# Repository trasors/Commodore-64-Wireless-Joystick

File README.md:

# Commodore 64 Wireless Joystick

A DIY wireless joystick system for the Commodore 64, using nRF24L01+ wireless modules and ATtiny/ATmega microcontrollers. The system consists of two main components:

* **Receiver (RX):** An ATtiny-based receiver that interfaces with the Commodore 64 dual joystick ports.
* **Transmitter (TX):** An ATmega-based wireless joystick controller.

## 1. Disclaimer

This project is provided **as-is**, without any guarantees of functionality or reliability etc. I built it in 2019 from various microcontrollers I was using at that time. It is not actively developed or maintained and uses hardware components and software libraries that are likely outdated. I am sharing as it may be useful for others for learning purposes or as a starting point to update and modernise. The useful bit is the C64 receiver PCB and code. The joystick / transmitter was mainly built for MAME use and the C64 receiver only handles a subset of the buttons.

## 2. Hardware Design

The EAGLE design files are located in the [`eagle/`](eagle/) directory. To modify, you may need to install the library file (.lbr)

### 2.1 Transmitter (TX)

The transmitter uses an ATmega328p microcontroller to read joystick inputs and send the corresponding button and directional states wirelessly via an nRF24L01+ transceiver. An MCP23008 was added to handle the extra buttons for MAME. A TP4056 module was added to charge a Lipo battery which powers the joystick.

| PCB Layout | Top | Bottom |
| --- | --- | --- |
|  |  |  |

### 2.2 Receiver (RX)

The receiver uses an ATtiny 1634 microcontroller and an nRF24L01+ transceiver to receive joystick data and translate it into signals compatible with the Commodore 64 joystick port. For more information on the pin mapping see [control port mapping](docs/C64ControlPort.md). Note, pots / analog axes are not implemented in the hardware.

| PCB Layout | Overview | Top | Bottom |
| --- | --- | --- | --- |
|  |  |  |  |

### 2.3 Bill of Materials (BOM)

Here is a list of the main components. Refer to the EAGLE schematics for exact component, values, quantities, and specifications etc.

#### Receiver
```
1 x ATTiny 1634
1 x nRF24L01+
1 x MCP1700 3.3V
2 x 9-pin D-SUB Female (PCB board mount variety)
```
#### Transmitter
```
1 x ATMega 328p QFP32
1 x nRF24L01+
1 x TP4056 (for LIPO battery and USB charging)
1 x Joystick, various buttons and a couple of pots
1 x MCP1700 3.3V
```
## 3. Firmware and Code

The firmware is located in the [`code/`](code/) directory. The code is divided into two main parts:

* **TX firmware:** Runs on the ATmega, reads the joystick inputs, and transmits their states over the nRF24 wireless link.
* **RX firmware:** Runs on the ATtiny, receives the wireless data, and translates it into the appropriate signals for the Commodore 64 joystick interface.

Notes on the [packet format](docs/PacketFormat.md):
* Analog axes are not implemented in the RX code
* Buttons 1-8 (except 5) register a button press on the C64 receiver
* Button 5 is used to toggle joystick 1 and 2 on the C64 receiver

### 3.1 Source Code

```text
code/
├── c64-wireless-joystick-tx/
│   └── c64-wireless-joystick-tx.ino
└── c64-wireless-joystick-rx/
    └── c64-wireless-joystick-rx.ino
```

### 3.2 Building and Uploading

The Arduino 1.8.8 IDE was use to compile the code.

### 3.3 Libraries and Dependencies

The firmware depends on the following external libraries: -

* https://github.com/nRF24/RF24
* https://github.com/spencekonde/attinycore
* https://github.com/adafruit/adafruit-mcp23008-library

*Note: This project uses the versions available in 2019/20. Current versions may not work!*

## 4. Hardware Build

Here are some pictures of the final build

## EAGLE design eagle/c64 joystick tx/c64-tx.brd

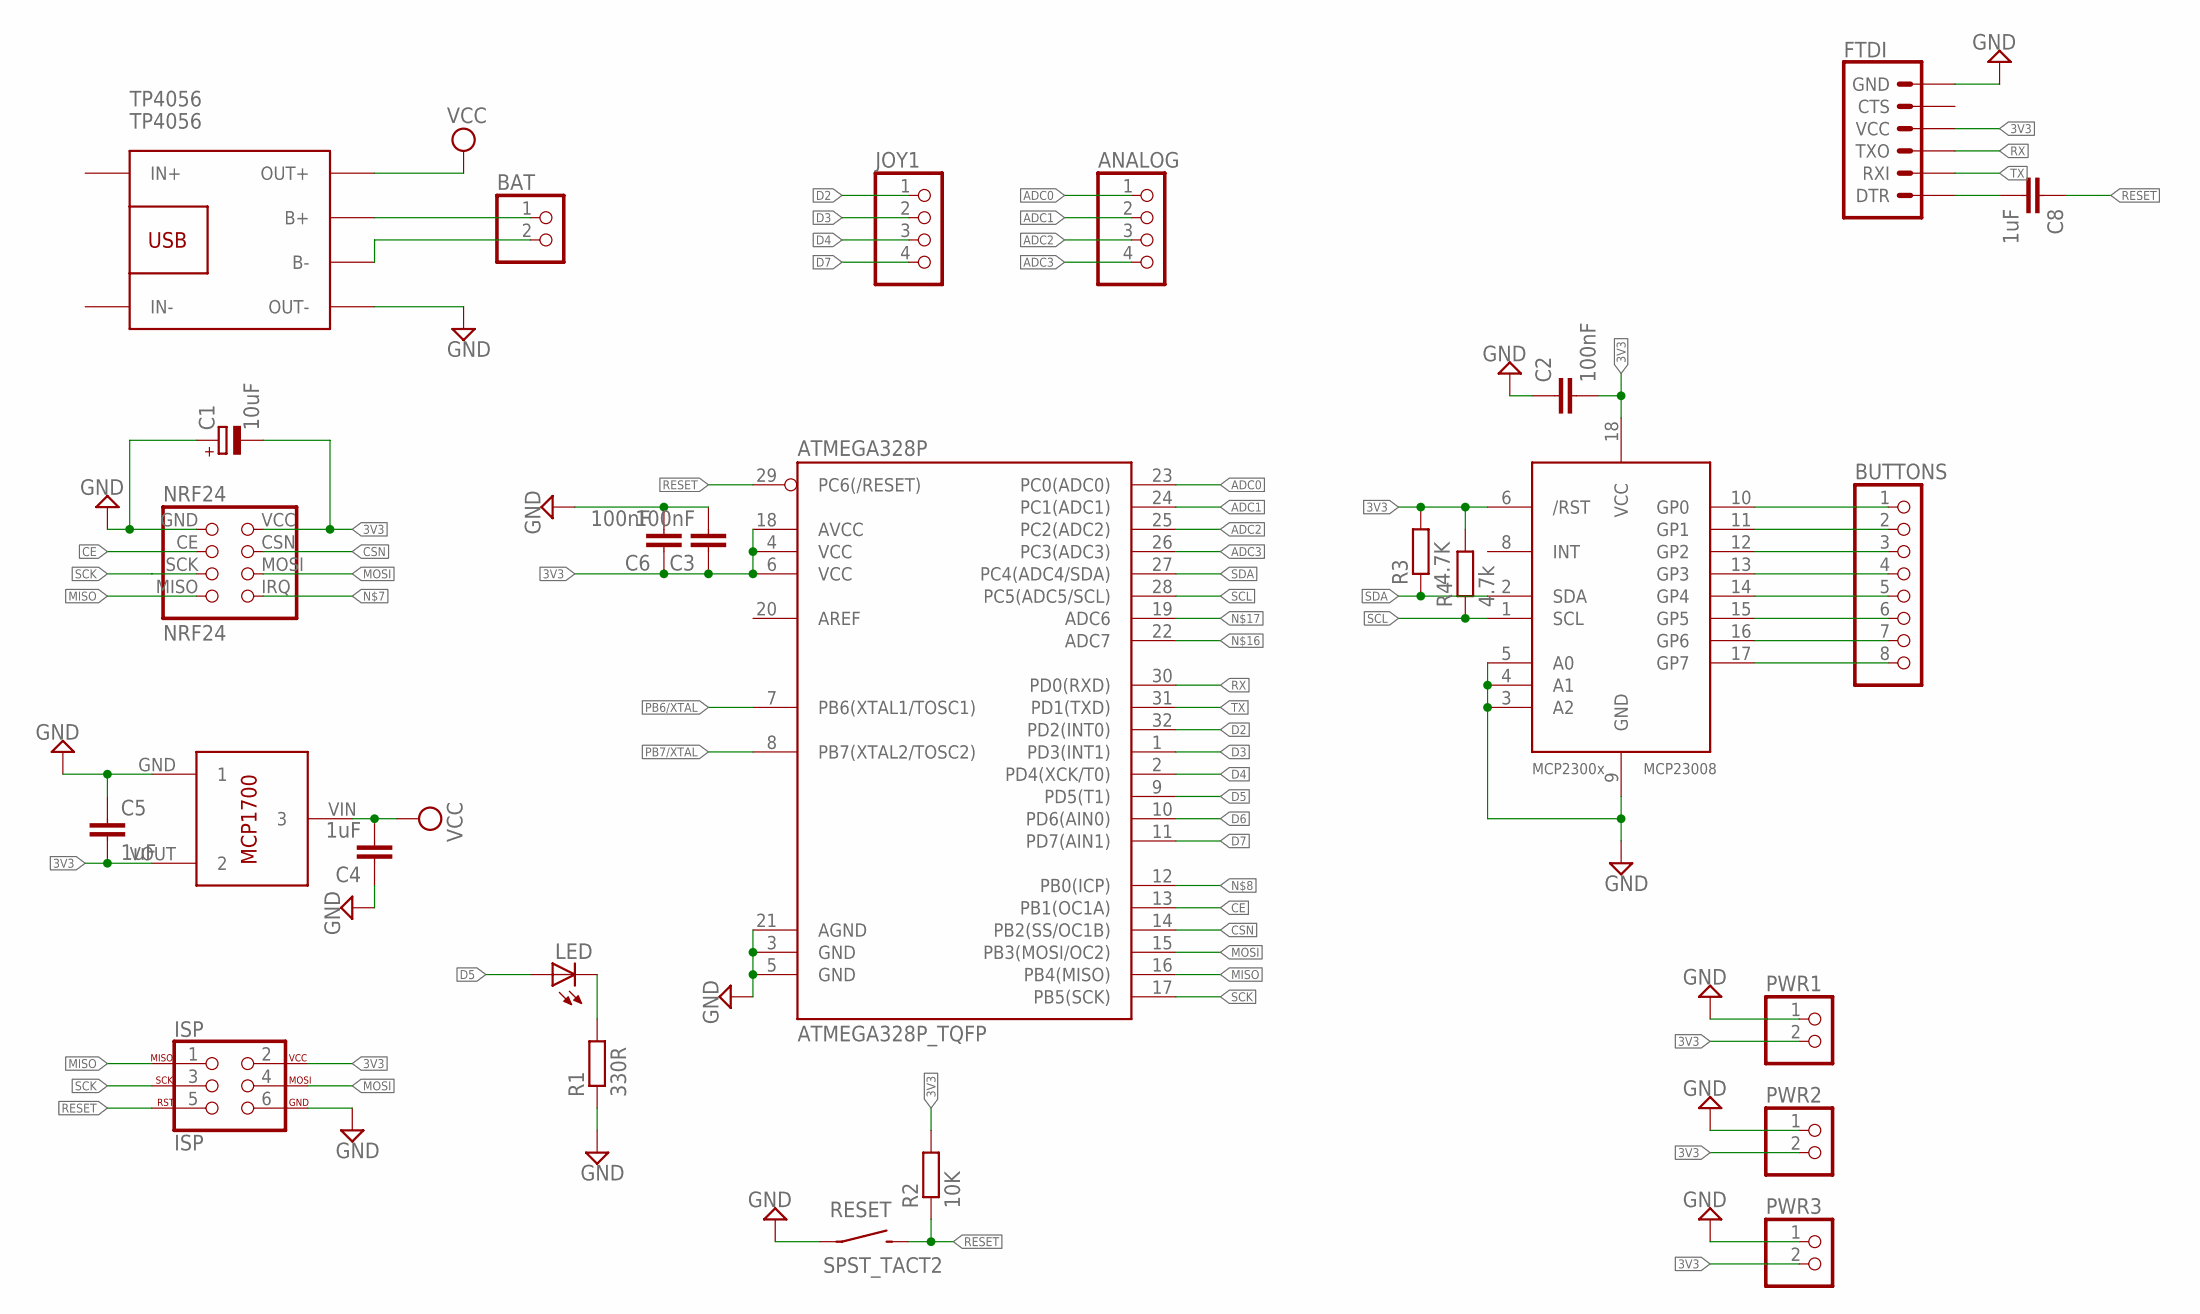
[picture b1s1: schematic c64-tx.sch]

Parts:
ANALOG: PINHD-1X4; 1X04
ATMEGA328P: ATMEGA328P_TQFP; TQFP32-08
BAT: PINHD-1X2; 1X02
BUTTONS: PINHD-1X8; 1X08
C1: 10uF; A/3216-18W
C2, C3, C6: 100nF; C1206K
C4, C5, C8: 1uF; C1206K
FTDI: 6_PIN_SERIAL_TARGETPTH-KIT; 1X06-KIT
ISP: ISP; 2X3-NS
JOY1: PINHD-1X4; 1X04
LED: LEDSMT1206; 1206
MCP1700: MCP1700T-3302E/TT
MCP23008: MCP23008/SO; SO18W
NRF24: NRF24; NRF24-PCB
PWR1, PWR2, PWR3: PINHD-1X2; 1X02
R1: 330R; M1206
R2: 10K; M1206
R3: 4.7K; M1206
R4: 4.7k; M1206
RESET: SPST_TACT2; 6MMTACTILE
TP4056: TP4056; BATTERY-CHARGER-LI-PROT

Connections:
3V3: ATMEGA328P.4 (VCC), ATMEGA328P.6 (VCC), ATMEGA328P.18 (AVCC), C1.-, C2.2, C3.1, C5.2, C6.1, FTDI.4 (VCC), ISP.2, MCP1700.VOUT (2), MCP23008.6 (/RST), MCP23008.18 (VCC), NRF24.VCC, PWR1.2, PWR2.2, PWR3.2, R2.2, R3.2, R4.2
ADC0: ANALOG.1, ATMEGA328P.23 (PC0(ADC0))
ADC1: ANALOG.2, ATMEGA328P.24 (PC1(ADC1))
ADC2: ANALOG.3, ATMEGA328P.25 (PC2(ADC2))
ADC3: ANALOG.4, ATMEGA328P.26 (PC3(ADC3))
B+: BAT.1, TP4056.B+
B-: BAT.2, TP4056.B-
CE: ATMEGA328P.13 (PB1(OC1A)), NRF24.CE
CSN: ATMEGA328P.14 (PB2(SS/OC1B)), NRF24.CSN
D2: ATMEGA328P.32 (PD2(INT0)), JOY1.1
D3: ATMEGA328P.1 (PD3(INT1)), JOY1.2
D4: ATMEGA328P.2 (PD4(XCK/T0)), JOY1.3
D5: ATMEGA328P.9 (PD5(T1)), LED.A
D6: ATMEGA328P.10 (PD6(AIN0))
D7: ATMEGA328P.11 (PD7(AIN1)), JOY1.4
GND: ATMEGA328P.3 (GND), ATMEGA328P.5 (GND), ATMEGA328P.21 (AGND), C1.+, C2.1, C3.2, C4.1, C5.1, C6.2, FTDI.6 (GND), ISP.6, MCP1700.GND (1), MCP23008.3 (A2), MCP23008.4 (A1), MCP23008.5 (A0), MCP23008.9 (GND), NRF24.GND, PWR1.1, PWR2.1, PWR3.1, R1.1, RESET.P$1, TP4056.OUT-
MISO: ATMEGA328P.16 (PB4(MISO)), ISP.1, NRF24.MISO
MOSI: ATMEGA328P.15 (PB3(MOSI/OC2)), ISP.4, NRF24.MOSI
unnamed: BUTTONS.1, MCP23008.10 (GP0)
unnamed: LED.C, R1.2
unnamed: BUTTONS.2, MCP23008.11 (GP1)
unnamed: BUTTONS.3, MCP23008.12 (GP2)
unnamed: BUTTONS.4, MCP23008.13 (GP3)
unnamed: BUTTONS.5, MCP23008.14 (GP4)
unnamed: BUTTONS.6, MCP23008.15 (GP5)
unnamed: BUTTONS.7, MCP23008.16 (GP6)
unnamed: BUTTONS.8, MCP23008.17 (GP7)
unnamed: C8.2, FTDI.1 (DTR)
PB6/XTAL: ATMEGA328P.7 (PB6(XTAL1/TOSC1))
PB7/XTAL: ATMEGA328P.8 (PB7(XTAL2/TOSC2))
RESET: ATMEGA328P.29 (PC6(/RESET)), C8.1, ISP.5, R2.1, RESET.P$2 (S)
RX: ATMEGA328P.30 (PD0(RXD)), FTDI.3 (TXO)
SCK: ATMEGA328P.17 (PB5(SCK)), ISP.3, NRF24.SCK
SCL: ATMEGA328P.28 (PC5(ADC5/SCL)), MCP23008.1 (SCL), R4.1
SDA: ATMEGA328P.27 (PC4(ADC4/SDA)), MCP23008.2 (SDA), R3.1
TX: ATMEGA328P.31 (PD1(TXD)), FTDI.2 (RXI)
VCC: C4.2, MCP1700.VIN (3), TP4056.OUT+

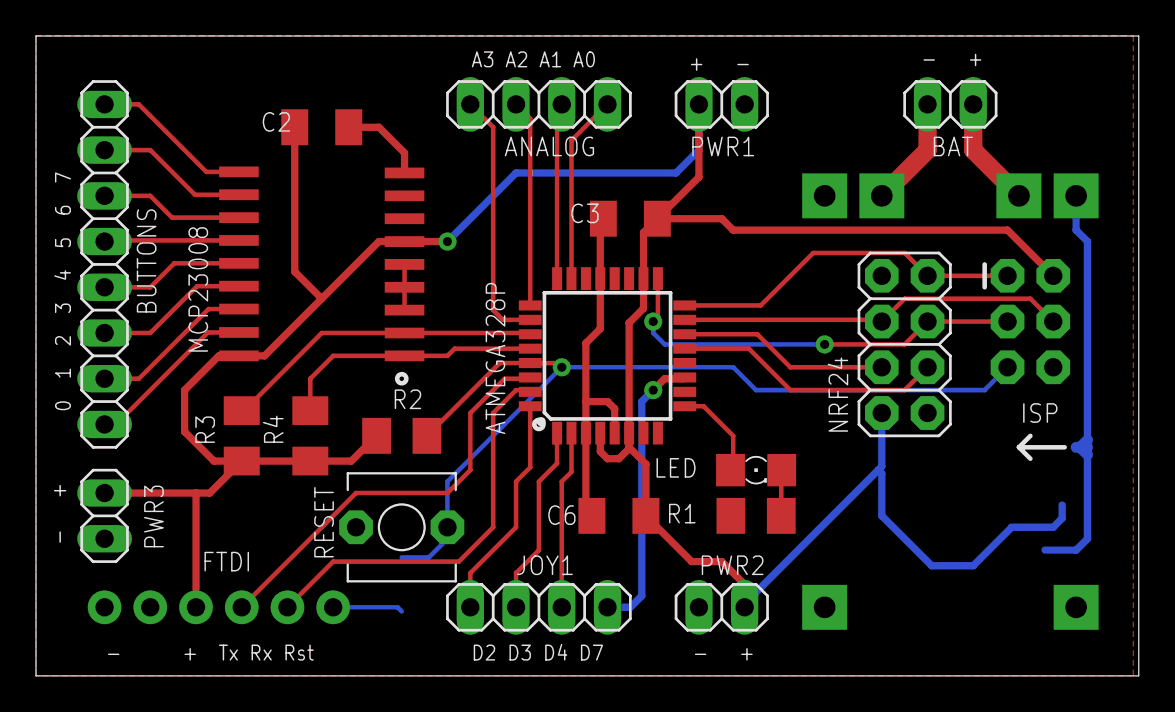
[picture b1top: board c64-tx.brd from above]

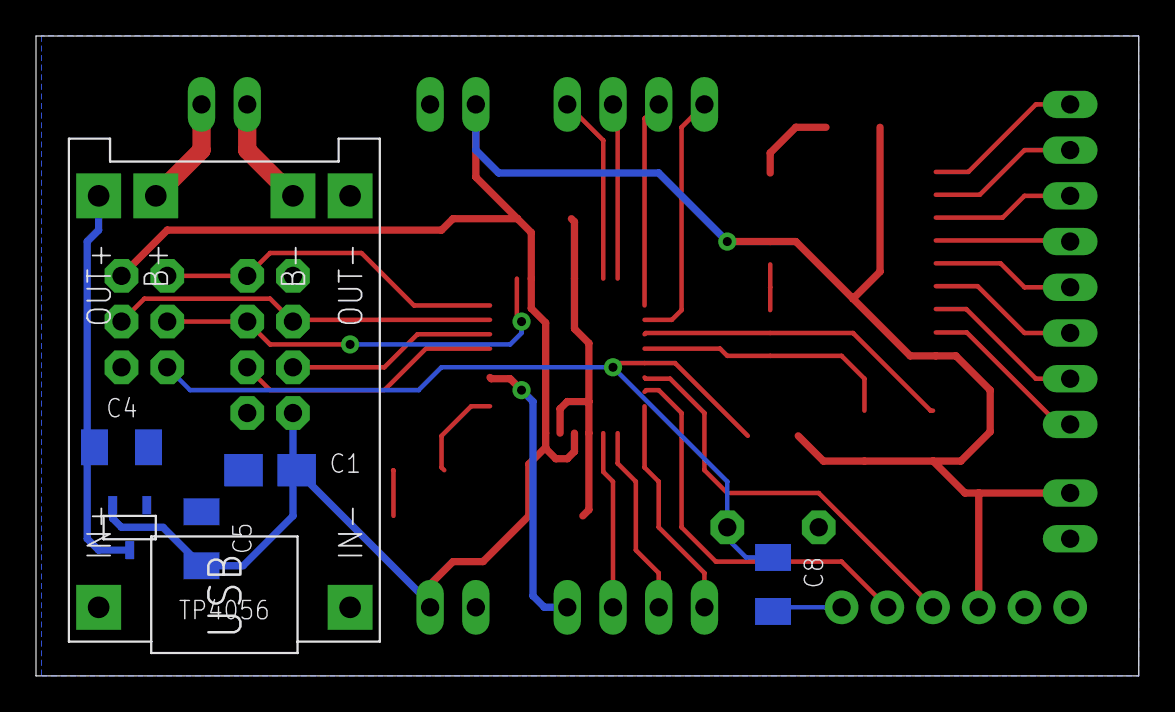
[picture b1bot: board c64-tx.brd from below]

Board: 2 copper layers, 61.3 x 35.5 mm, 27 parts (6 on the bottom side), 34 nets.

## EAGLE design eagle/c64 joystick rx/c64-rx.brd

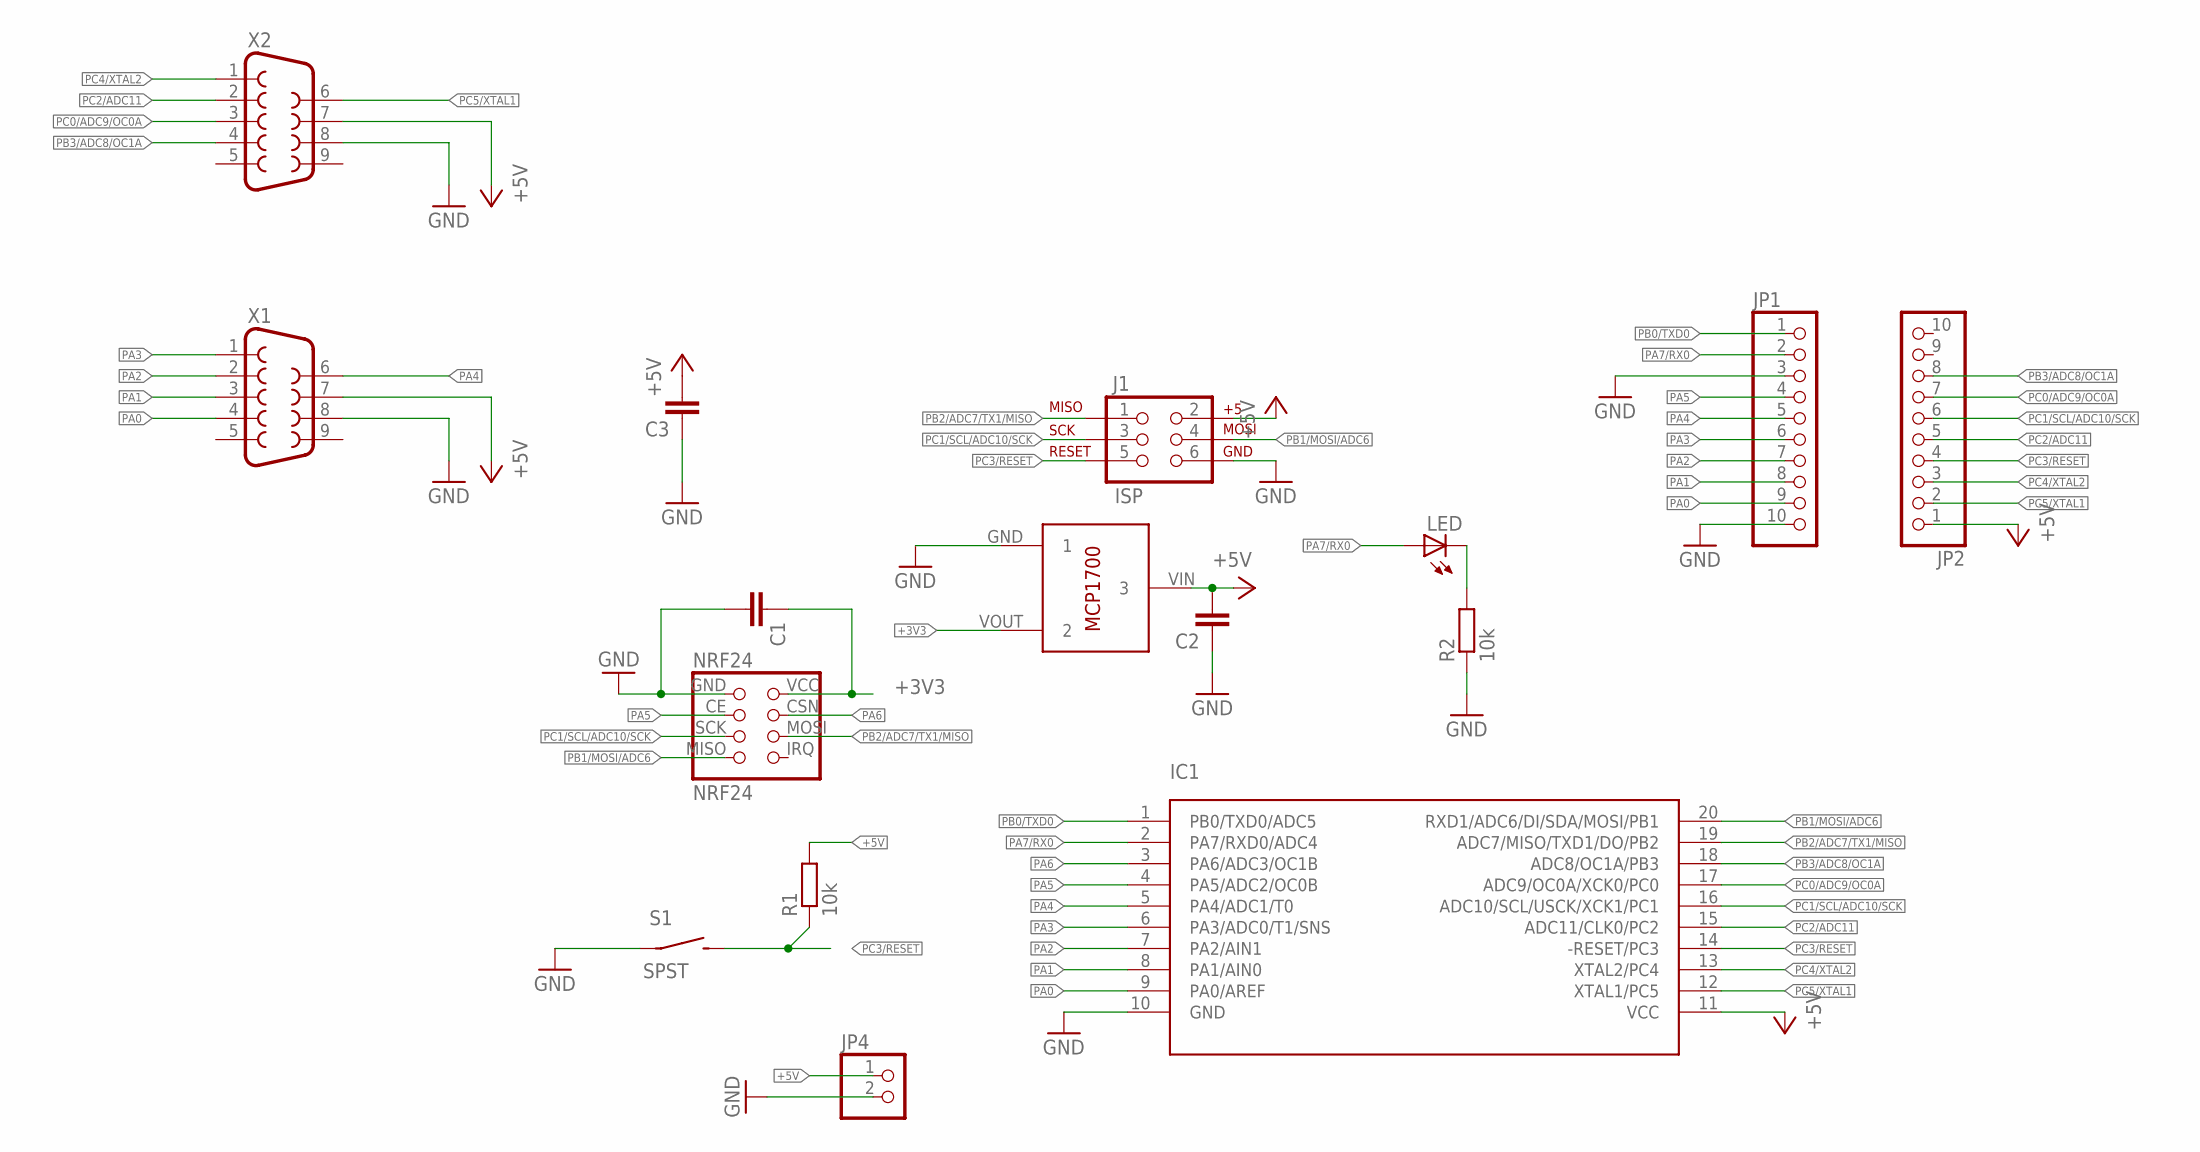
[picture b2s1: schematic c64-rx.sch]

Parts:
C1, C2, C3: C-EUC1206K; C1206K
IC1: ATTINY1634; SOIC20
J1: ISP; 2X3-NS
JP1, JP2: PINHD-1X10; 1X10
JP4: PINHD-1X2; 1X02
LED: LEDSMT1206; 1206
NRF24: NRF24
R1, R2: 10k; M1206
S1: SPST; OFFBOARD_2_LG
U$3: MCP1700T-3302E/TT
X1, X2: F09D

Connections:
+3V3: C1.1, NRF24.VCC, U$3.VOUT (2)
+5V: C2.2, C3.2, IC1.11 (VCC), J1.2, JP2.1, JP4.1, R1.2, U$3.VIN (3), X1.7, X2.7
GND: C1.2, C2.1, C3.1, IC1.10 (GND), J1.6, JP1.3, JP1.10, JP4.2, NRF24.GND, R2.1, S1.P$1, U$3.GND (1), X1.8, X2.8
unnamed: LED.C, R2.2
PA0: IC1.9 (PA0/AREF), JP1.9, X1.4
PA1: IC1.8 (PA1/AIN0), JP1.8, X1.3
PA2: IC1.7 (PA2/AIN1), JP1.7, X1.2
PA3: IC1.6 (PA3/ADC0/T1/SNS), JP1.6, X1.1
PA4: IC1.5 (PA4/ADC1/T0), JP1.5, X1.6
PA5: IC1.4 (PA5/ADC2/OC0B), JP1.4, NRF24.CE
PA6: IC1.3 (PA6/ADC3/OC1B), NRF24.CSN
PA7/RX0: IC1.2 (PA7/RXD0/ADC4), JP1.2, LED.A
PB0/TXD0: IC1.1 (PB0/TXD0/ADC5), JP1.1
PB1/MOSI/ADC6: IC1.20 (RXD1/ADC6/DI/SDA/MOSI/PB1), J1.4, NRF24.MISO
PB2/ADC7/TX1/MISO: IC1.19 (ADC7/MISO/TXD1/DO/PB2), J1.1, NRF24.MOSI
PB3/ADC8/OC1A: IC1.18 (ADC8/OC1A/PB3), JP2.8, X2.4
PC0/ADC9/OC0A: IC1.17 (ADC9/OC0A/XCK0/PC0), JP2.7, X2.3
PC1/SCL/ADC10/SCK: IC1.16 (ADC10/SCL/USCK/XCK1/PC1), J1.3, JP2.6, NRF24.SCK
PC2/ADC11: IC1.15 (ADC11/CLK0/PC2), JP2.5, X2.2
PC3/RESET: IC1.14 (-RESET/PC3), J1.5, JP2.4, R1.1, S1.P$2 (S)
PC4/XTAL2: IC1.13 (XTAL2/PC4), JP2.3, X2.1
PC5/XTAL1: IC1.12 (XTAL1/PC5), JP2.2, X2.6

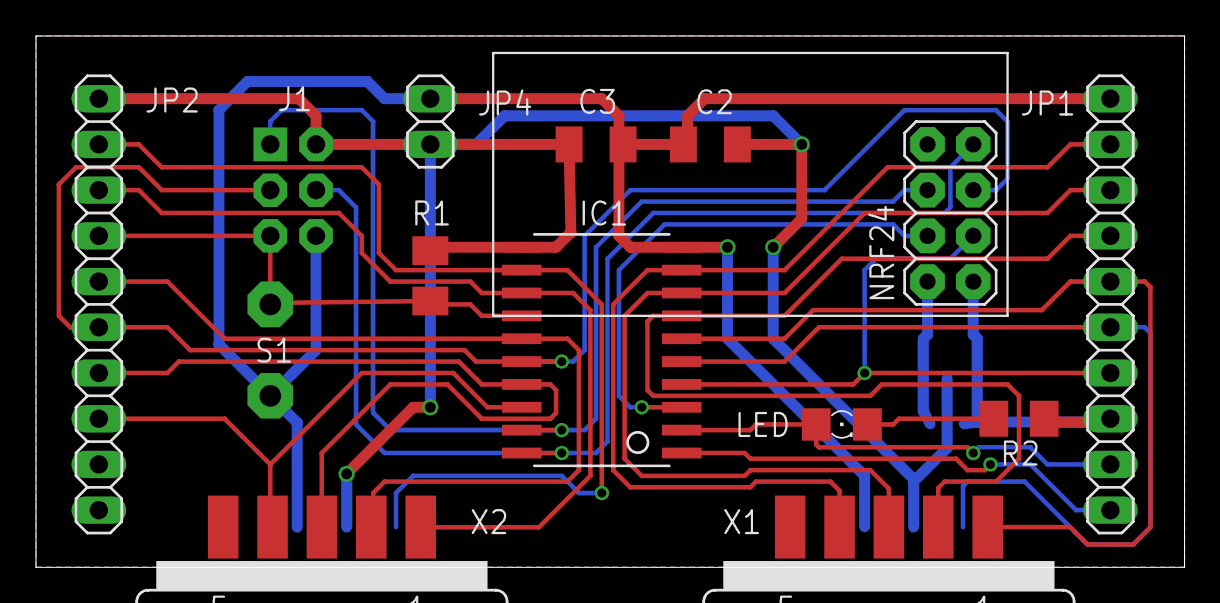
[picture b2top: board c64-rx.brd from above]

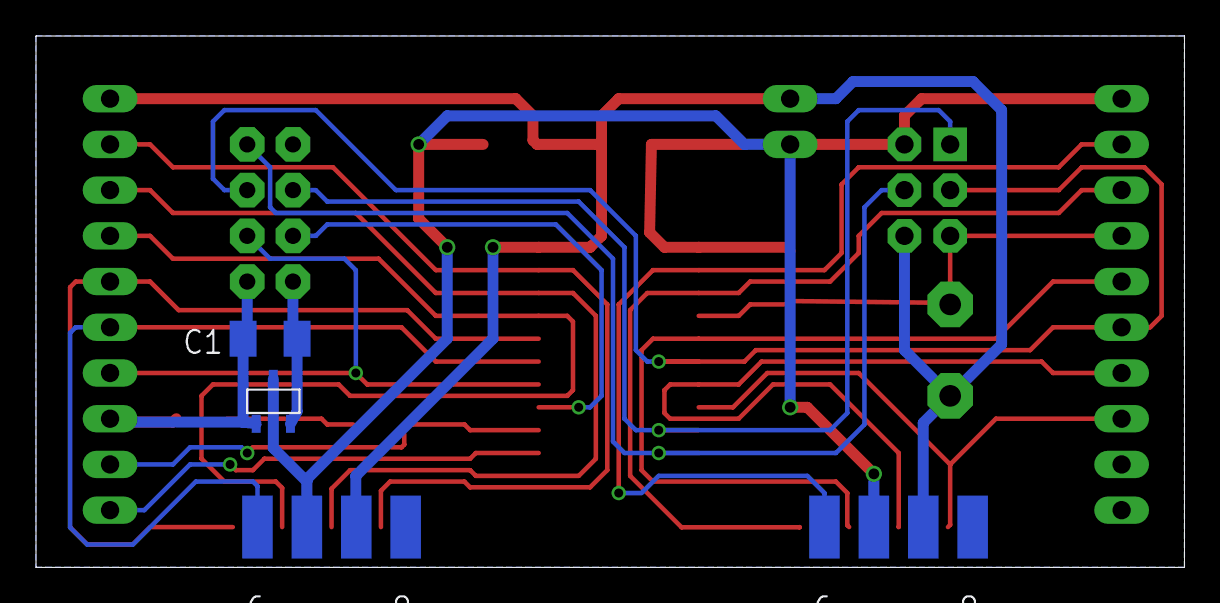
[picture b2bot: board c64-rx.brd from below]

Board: 2 copper layers, 63.8 x 29.5 mm, 16 parts (2 on the bottom side), 22 nets.

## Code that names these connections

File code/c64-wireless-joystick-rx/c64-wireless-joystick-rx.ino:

/*
// ATMEL ATTINY1634
//
//                   +-\/-+
// TX   (D  0) PB0  1|    |20  PB1 (D  16)
// RX   (D  1) PA7  2|    |19  PB2 (D  15)
//    * (D  2) PA6  3|    |18  PB3 (D  14) *
//    * (D  3) PA5  4|    |17  PC0 (D  13) *
//      (D  4) PA4  5|    |16  PC1 (D  12)
//      (D  5) PA3  6|    |15  PC2 (D  11)
//      (D  6) PA2  7|    |14  PC3/RESET (D 17)
//      (D  7) PA1  8|    |13  PC4 (D  10)
//      (D  8) PA0  9|    |12  PC5 (D  9)
//             GND 10|    |11  VCC
//                   +----+
//
// Reminder: Pins 6 - 1 & 20 - 15 are ADC pins
// * indicates PWM port
// these arrays map port names (e.g. port B) to the
// appropriate addresses for various functions (e.g. reading
// and writing)
 *
 * NRF24L01 / ATTINY1634
 * PIN 1  GND  -> GND
 * PIN 2  VCC  -> 3V3
 * PIN 3  CE   -> 4  / PA5 / D3
 * PIN 4  CSN  -> 3  / PA6 / D2
 * PIN 5  SCK  -> 16 / PC1
 * PIN 6  MOSI -> 19 / PB2
 * PIN 7  MISO -> 20 / PB1
 * PIN 8  IRQ  -> N/C
 * 
 * Notes
 * http://atariage.com/forums/topic/232752-5v-to-atari-joystick-ports/
 * https://www.c64-wiki.com/wiki/64JPX
 * https://github.com/svofski/mouse1351/blob/master/c1351.c
 * http://atariage.com/forums/blog/572/entry-11529-nunchuk-arduino-atari-joystick/ (photocoupler)
 * 
 */

// #define DEBUG // must uncomment #define SERIAL_DEBUG, line 19 RF24_config.h
#define RADIO

#if defined( DEBUG )
  #define DEBUG_STREAM  Serial
#endif

// nrf setup
#if defined( RADIO )
  #define CE_PIN 3  // PA5
  #define CSN_PIN 2 // PA6
  #include "RF24.h"
  RF24 radio(CE_PIN, CSN_PIN);
  byte addresses[][6] = { "j1tx","j1rx" };
#endif

/*
 * Digispark Joystick
 * 0 - X Axis (0=L, 255=R)
 * 1 - Y Axis (0=U, 255=D)
 * 2 - Analog 1
 * 3 - Analog 2
 * 4 - 6 Not used
 * 7 - Buttons (1B, 2P, 4B, 8P, 16Y, 32Y, 64B, 128P) B=Blue, P=Pink, Y=Yellow
 * 
 * C64 Joystick Port
 * Pin  Direction   Port 1  Port 2
 * 1    Up          PA3     PC4
 * 2    Down        PA2     PC2
 * 3    Left        PA1     PC0
 * 4    Right       PA0     PB3
 * 5    Pot A
 * 6    Button      PA4     PC5
 * 7    +5V 100Ma
 * 8    GND
 * 9    Pot B
 *
 * DB9 header
 * Pin  Direction
 * 1    GND
 * 2    +5V
 * 3    Button
 * 4    Up
 * 5    Down
 * 6    Left
 * 7    Right
 * 
 */

// PORT A
#define JOY1_L 1
#define JOY1_R 0
#define JOY1_U 3
#define JOY1_D 2
#define JOY1_B 4

// PORT B
#define JOY2_R 3

// PORT C
#define JOY2_L 0
#define JOY2_U 4
#define JOY2_D 2
#define JOY2_B 5

#define LED_PIN 1

byte receive_payload[32];

bool joy_toggle = false; // default to joy2

void reset_joy_1() {
  // we want the pins to be reset
  DDRA &= ~( (1 << JOY1_L) | (1 << JOY1_R) | (1 << JOY1_U) | (1 << JOY1_D) | (1 << JOY1_B) ); // input
}

void reset_joy_2() {
  // we want the pins to be reset
  DDRB &= ~  (1 << JOY2_R);
  DDRC &= ~( (1 << JOY2_L) | (1 << JOY2_U) | (1 << JOY2_D) | (1 << JOY2_B) ); // input
}

void setup() {

/*
 * DDR PORT
 * 0    0  - input, high impedance
 * 0    1  - input, pulled up
 * 1    0  - output, driven low
 * 1    1  - output, driven high
 * 
 * INPUT:  DDRx &= ~( pin | pin ) 
 * OUTPUT: DDRx |= pin | pin
 * LOW:  PORTx &= ~
 * HIGH: PORTx |=
 * 
 */
  DDRA &= ~( (1 << JOY1_L) | (1 << JOY1_R) | (1 << JOY1_U) | (1 << JOY1_D) | (1 << JOY1_B) ); // input
  PORTA &= ~( (1 << JOY1_L) | (1 << JOY1_R) | (1 << JOY1_U) | (1 << JOY1_D) | (1 << JOY1_B) );// high impedance

  DDRC &= ~( (1 << JOY2_L) | (1 << JOY2_U) | (1 << JOY2_D) | (1 << JOY2_B) ); // input
  PORTC &= ~( (1 << JOY2_L) | (1 << JOY2_U) | (1 << JOY2_D) | (1 << JOY2_B) );// high impedance
  DDRB &= ~(1 << JOY2_R);
  PORTB &= ~(1 << JOY2_R);

  pinMode(LED_PIN, OUTPUT);
  #if defined(DEBUG)
  pinMode(LED_PIN, OUTPUT);
  DEBUG_STREAM.begin(9600);
  #endif
  
  // setup nrf24
  #if defined( RADIO )
  radio.begin();
  radio.setPALevel(RF24_PA_HIGH);
  radio.setAutoAck(1); 
  radio.setChannel(95);
  radio.setRetries(15,15);
  radio.enableDynamicPayloads();
  //radio.setCRCLength(RF24_CRC_16);
  radio.setDataRate(RF24_250KBPS);
  radio.openWritingPipe(addresses[0]);
  radio.openReadingPipe(1,addresses[1]);
  radio.startListening();
  #endif
  
  #if defined( DEBUG )
  DEBUG_STREAM.print(F("C64JX Debug"));
  //radio.printDetails();
  #endif
while(0);
}

void loop() {
  
  uint8_t len = 0;
  #if defined( RADIO )
  if ( radio.available() ) {
    while (radio.available()) {
      len = radio.getDynamicPayloadSize();
      if( !len ) return;
      radio.read( &receive_payload, len );
      #if defined( DEBUG )
      for(int i=0;i<len;i++) {
        DEBUG_STREAM.print(receive_payload[i]);
      } // end for
      digitalWrite(LED_PIN, HIGH);   // turn the LED on (HIGH is the voltage level)
      delay(25);
      digitalWrite(LED_PIN, LOW);
      #endif

      if( receive_payload[7] == 16 ) {
        digitalWrite(LED_PIN, HIGH);   // turn the LED on (HIGH is the voltage level)
        delay(250);
        digitalWrite(LED_PIN, LOW);
        joy_toggle = !joy_toggle;
        reset_joy_1();
        reset_joy_2();
      }

      if( joy_toggle ) {
      (receive_payload[0] < 127) ? DDRA |= (1 << JOY1_L) : DDRA &= ~( (1 << JOY1_L) ); // LEFT?
      (receive_payload[0] > 127) ? DDRA |= (1 << JOY1_R) : DDRA &= ~( (1 << JOY1_R) ); // RIGHT?
      (receive_payload[1] < 127) ? DDRA |= (1 << JOY1_U) : DDRA &= ~( (1 << JOY1_U) ); // UP?
      (receive_payload[1] > 127) ? DDRA |= (1 << JOY1_D) : DDRA &= ~( (1 << JOY1_D) ); // DOWN?
      (receive_payload[7] > 0  ) ? DDRA |= (1 << JOY1_B) : DDRA &= ~( (1 << JOY1_B) ); // BUTTON?
      } else {
      (receive_payload[0] < 127) ? DDRC |= (1 << JOY2_L) : DDRC &= ~( (1 << JOY2_L) ); // LEFT?
      (receive_payload[0] > 127) ? DDRB |= (1 << JOY2_R) : DDRB &= ~( (1 << JOY2_R) ); // RIGHT?
      (receive_payload[1] < 127) ? DDRC |= (1 << JOY2_U) : DDRC &= ~( (1 << JOY2_U) ); // UP?
      (receive_payload[1] > 127) ? DDRC |= (1 << JOY2_D) : DDRC &= ~( (1 << JOY2_D) ); // DOWN?
      (receive_payload[7] > 0  ) ? DDRC |= (1 << JOY2_B) : DDRC &= ~( (1 << JOY2_B) ); // BUTTON?
      } // end if
 
    } // end while
  } // end if
  #endif
//delay(1000);
//DEBUG_STREAM.println(".");

}

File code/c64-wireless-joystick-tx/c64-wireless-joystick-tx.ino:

/*
 * ATMEGA328PB
 *
 * NRF24L01
 * CE   -> PB1, D9
 * CSN  -> PB2, D10
 * MOSI -> PB3, D11
 * SCK  -> PB5, D12
 * MISO -> PB4, D13
 * 
 * MCP23008
 * Address 0x20
 * 
 * LED -> PD5, D5
 * 
 * 
 */
 
#define DEBUG
#define RADIO
#define PIN_LED 5
#define NO_GPIO_PINS 8

// Adafruit MCP23008 library
#include "Adafruit_MCP23008.h"
Adafruit_MCP23008 mcp;

#if defined(RADIO)
#include "RF24.h"
#define CE_PIN 9
#define CSN_PIN 10
RF24 radio(CE_PIN, CSN_PIN);
byte addresses[][6] = { "j1tx","j1rx" };
#endif

#if defined(DEBUG)
#define SERIAL_DEBUG
#include <printf.h>
#endif

// PORTD Joystick
#define JOY_LEFT 2
#define JOY_RIGHT 7
#define JOY_DOWN 4
#define JOY_UP 3

// PORTC Buttons
//#define BUT_1 2
//#define BUT_2 3

// Analog pins
#define ANALOG1 A0
#define ANALOG2 A1
int analogOldVal1, analogOldVal2, analogNewVal1, analogNewVal2;

int timeout = 0;
int threshold = 5;

byte switchVar1 = 72;  //01001000
unsigned int  btnBits = 0;

// joystick buffer
byte joystick[] = { 127, 127, 127, 127, 127, 127, 0, 0 };
byte joystick_old[] = { 0, 0, 0, 0, 0, 0, 0, 0 };
int sz = sizeof(joystick);
#define JOY_X 0
#define JOY_Y 1
#define ROT_X 2
#define ROT_Y 3
#define ROT_Z 4
#define SLIDER 5
#define BUTTONS_1 6
#define BUTTONS_2 7

void setup() {
  
  #if defined(DEBUG)
  Serial.begin( 115200 );
  Serial.println("Starting...");
  printf_begin();
  #endif  

  // MCP23008 setup
  mcp.begin();
  for(int i=0;i<NO_GPIO_PINS;i++) {
    mcp.pinMode(i, INPUT);
    mcp.pullUp(i, HIGH);  // turn on a 100K pullup internally
  }
  
  // Joystick pins setup
  // Configure Joystick pins for input
  DDRD &= ~( (1 << JOY_LEFT) | (1 << JOY_RIGHT) | (1 << JOY_UP) | (1 << JOY_DOWN) );
  // Confgure Joystick pins as input_pullup
  PORTD |= ( (1 << JOY_LEFT) | (1 << JOY_RIGHT) | (1 << JOY_UP) | (1 << JOY_DOWN) );

  // Buttons pins setup
  // Configure button pins for input
  //DDRC &= ~( (1 << BUT_1) | (1 << BUT_2) );
  // Confgure Joystick pins as input_pullup
  //PORTC |= ( (1 << BUT_1) | (1 << BUT_2) );

  // setup nrf24
  #if defined(RADIO)
  radio.begin();
  radio.setPALevel(RF24_PA_HIGH);
  radio.setAutoAck(1); 
  radio.setChannel(95);
  radio.setRetries(15,15);
  radio.enableDynamicPayloads();
  //radio.setCRCLength(RF24_CRC_16);
  radio.setDataRate(RF24_250KBPS);
  radio.openWritingPipe(addresses[1]);
  radio.openReadingPipe(1,addresses[0]);
  #endif
  #if defined(DEBUG)
  #if defined(RADIO)
  radio.printDetails();
  #endif
  #endif
  delay(1000);
}

void loop() {
  
  // status
  int pressed = 0;

  // Read MCP23008 GPIO ports (note 1=open)
  switchVar1 = 255 - mcp.readGPIO();

  // Read GPIO buttons
  btnBits = switchVar1;
  if(btnBits) {
    joystick[BUTTONS_2] = btnBits;
  } else {
    joystick[BUTTONS_2] = 0;
  } // end if
  
  // Read joystick
  /*
  Serial.println(!(PIND & (1 << JOY_LEFT)));
  Serial.println(!(PIND & (1 << JOY_RIGHT)));
  Serial.println(!(PIND & (1 << JOY_UP)));
  Serial.println(!(PIND & (1 << JOY_DOWN)));
  */
  !(PIND&(1 << JOY_LEFT)) ? joystick[JOY_X] = 0 : (!(PIND&(1 << JOY_RIGHT)) ? joystick[JOY_X] = 255 : joystick[JOY_X] = 127);
  !(PIND&(1 << JOY_UP)) ? joystick[JOY_Y] = 0 : (!(PIND&(1 << JOY_DOWN)) ? joystick[JOY_Y] = 255 : joystick[JOY_Y] = 127);

  // Read PORTC buttons
  //Serial.println( (PINC & (1 << BUT_1)) );
  //Serial.println( (PINC & (1 << BUT_2)) );

  // Read analog inputs
  analogNewVal1 = analogRead(ANALOG1)>>2;
  analogNewVal2 = analogRead(ANALOG2)>>2;
  if (analogNewVal1 > analogOldVal1 + 2 || analogNewVal1 < analogOldVal1 - 2) {
    joystick[ROT_X] = analogNewVal1;
    analogOldVal1 = analogNewVal1;
  } // end if
  if (analogNewVal2 > analogOldVal2 + 2 || analogNewVal2 < analogOldVal2 - 2) {
    joystick[ROT_Y] = analogNewVal2;
    analogOldVal2 = analogNewVal2;
  } // end if

  // compare with old values
  for(int i=0; i<sz; i++) {
    if( joystick_old[i] != joystick[i] )
      pressed = 1;
    joystick_old[i] = joystick[i];
  } // end for

  // send data only if change
  if( pressed ) {
    #if defined(RADIO)
    if( !radio.write( &joystick, sz ) ) {
      #if defined(DEBUG)
      Serial.println(F("send failed"));
      #endif
    } else {
      #if defined(DEBUG)
      Serial.println(F("sent"));
      #endif
    } // end if
    #endif*/
    #ifdef DEBUG
    for(int i=0; i<sz; i++) {
      Serial.print(joystick[i]);
      Serial.print(" ");
    } // end for
    Serial.println("");
    #endif
  } // end if

  delay(20);
}

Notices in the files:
parts and their libraries:
SparkFun-Connectors: Licensing: CC v3.0 Share-Alike You are welcome to use this library for commercial purposes.
SparkFun-DigitalIC: Licensing: Creative Commons ShareAlike 4.0 International - https://creativecommons.org/licenses/by-sa/4.0
